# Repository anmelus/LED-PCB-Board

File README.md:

## LED Board project

This project demonstrates the design and development of a custom LED board, starting from PCB creation using KiCAD to writing the software that powers it. Below, you'll find details on how the project is structured and how to get started.

### Overview

This project involves the complete design and implementation of a custom LED board. It includes:

1. The PCB Design created using KiCAD.
2. The software to control the LED board, providing functionality such as LED patterns, brightness control, and more.

This repository serves as a resource for hobbyists and developers who want to understand the process of creating hardware and writing corresponding software.

### Features

Features

* Custom PCB Design: Created using KiCAD for a fully custom LED board.
* Software Integration: Firmware/software to control LEDs with custom patterns and behavior.
* Modular Design: Easy to modify and expand upon.

Images of the schematics and final result are available in /electrical/LEDboard/Images

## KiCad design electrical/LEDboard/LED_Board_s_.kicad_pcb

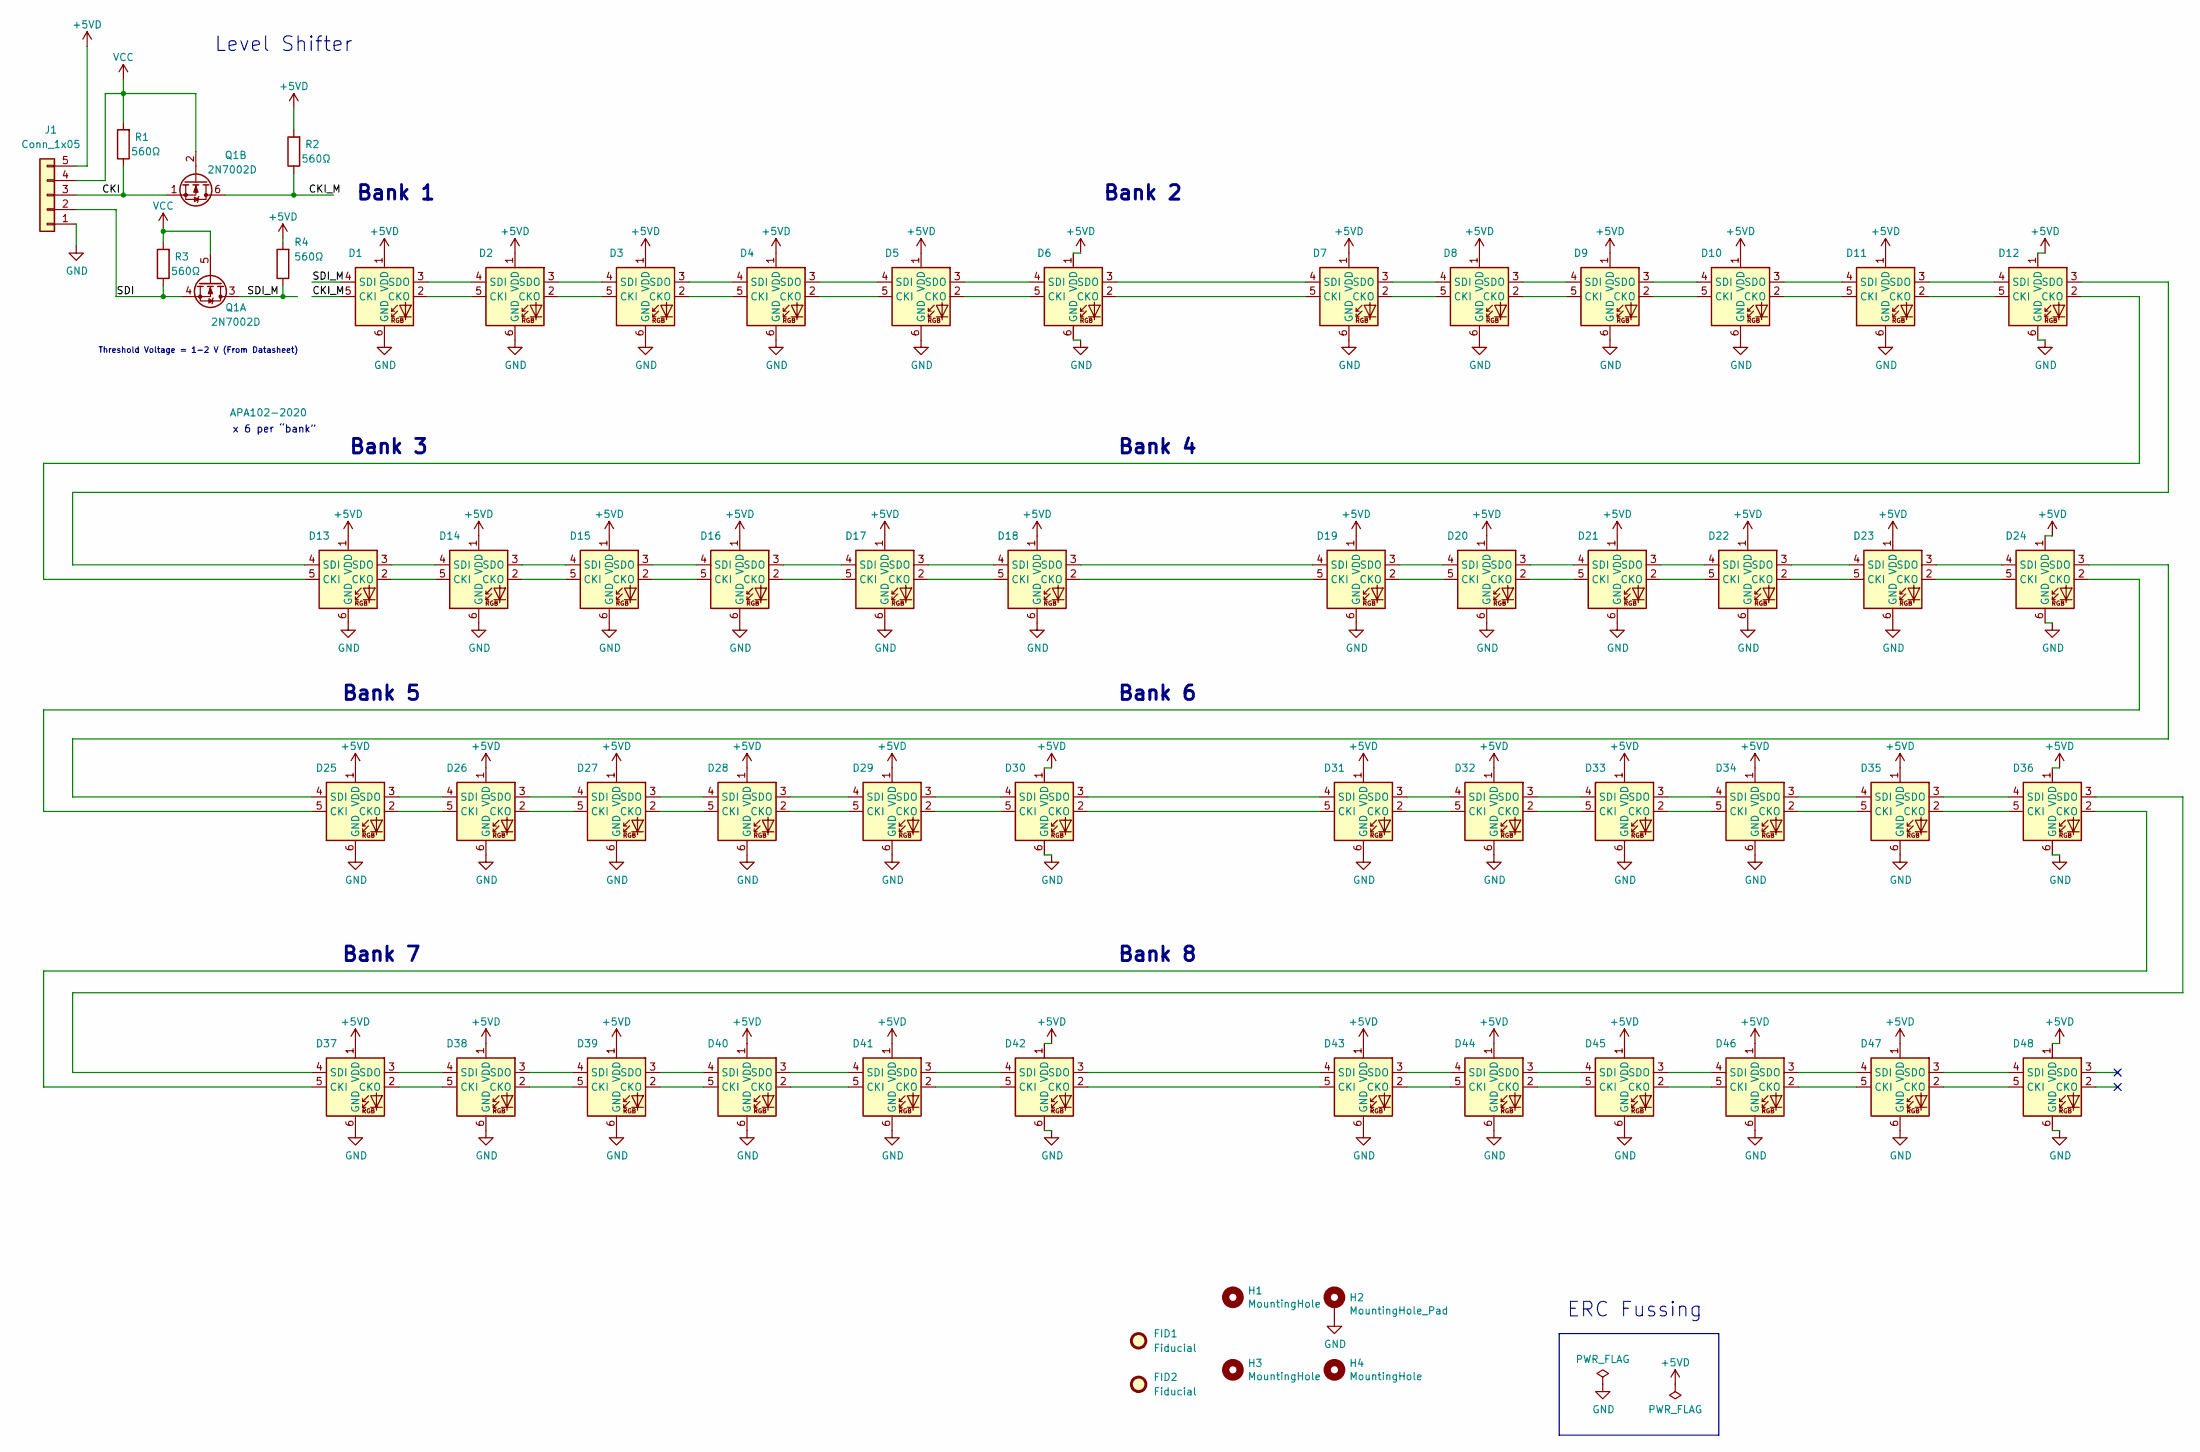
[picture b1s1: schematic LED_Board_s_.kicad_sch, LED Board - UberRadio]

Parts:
D1, D2, D3, D4, D5, D6, D7, D8, D9, D10, D11, D12, D13, D14, D15, D16, D17, D18, D19, D20, D21, D22, D23, D24, D25, D26, D27, D28, D29, D30, D31, D32, D33, D34, D35, D36, D37, D38, D39, D40, D41, D42, D43, D44, D45, D46, D47, D48: APA102-2020; LED-APA102-2020
FID1, FID2: Fiducial; Fiducial_0.5mm_Mask1mm
H1, H3, H4: MountingHole; MountingHole_3.5mm_Pad
H2: MountingHole_Pad; MountingHole_3.5mm_Pad_Via
J1: Conn_1x05; PinHeader_1x05_P2.54mm_Vertical
Q1: 2N7002D; SOT-23-6
R1, R2, R3, R4: 560Ω; R_1206_3216Metric_Pad1.30x1.75mm_HandSolder

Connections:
+5VD: D1.1 (VDD), D2.1 (VDD), D3.1 (VDD), D4.1 (VDD), D5.1 (VDD), D6.1 (VDD), D7.1 (VDD), D8.1 (VDD), D9.1 (VDD), D10.1 (VDD), D11.1 (VDD), D12.1 (VDD), D13.1 (VDD), D14.1 (VDD), D15.1 (VDD), D16.1 (VDD), D17.1 (VDD), D18.1 (VDD), D19.1 (VDD), D20.1 (VDD), D21.1 (VDD), D22.1 (VDD), D23.1 (VDD), D24.1 (VDD), D25.1 (VDD), D26.1 (VDD), D27.1 (VDD), D28.1 (VDD), D29.1 (VDD), D30.1 (VDD), D31.1 (VDD), D32.1 (VDD), D33.1 (VDD), D34.1 (VDD), D35.1 (VDD), D36.1 (VDD), D37.1 (VDD), D38.1 (VDD), D39.1 (VDD), D40.1 (VDD), D41.1 (VDD), D42.1 (VDD), D43.1 (VDD), D44.1 (VDD), D45.1 (VDD), D46.1 (VDD), D47.1 (VDD), D48.1 (VDD), J1.5, R2.2, R4.2
/CKI: J1.3, Q1.1 (S), R1.1
/CKI_M: D1.5 (CKI), Q1.6 (D), R2.1
/SDI: J1.2, Q1.4 (S), R3.1
/SDI_M: D1.4 (SDI), Q1.3 (D), R4.1
GND: D1.6 (GND), D2.6 (GND), D3.6 (GND), D4.6 (GND), D5.6 (GND), D6.6 (GND), D7.6 (GND), D8.6 (GND), D9.6 (GND), D10.6 (GND), D11.6 (GND), D12.6 (GND), D13.6 (GND), D14.6 (GND), D15.6 (GND), D16.6 (GND), D17.6 (GND), D18.6 (GND), D19.6 (GND), D20.6 (GND), D21.6 (GND), D22.6 (GND), D23.6 (GND), D24.6 (GND), D25.6 (GND), D26.6 (GND), D27.6 (GND), D28.6 (GND), D29.6 (GND), D30.6 (GND), D31.6 (GND), D32.6 (GND), D33.6 (GND), D34.6 (GND), D35.6 (GND), D36.6 (GND), D37.6 (GND), D38.6 (GND), D39.6 (GND), D40.6 (GND), D41.6 (GND), D42.6 (GND), D43.6 (GND), D44.6 (GND), D45.6 (GND), D46.6 (GND), D47.6 (GND), D48.6 (GND), H2.1, J1.1
unnamed: D1.2 (CKO), D2.5 (CKI)
unnamed: D1.3 (SDO), D2.4 (SDI)
unnamed: D2.2 (CKO), D3.5 (CKI)
unnamed: D2.3 (SDO), D3.4 (SDI)
unnamed: D3.2 (CKO), D4.5 (CKI)
unnamed: D3.3 (SDO), D4.4 (SDI)
unnamed: D4.2 (CKO), D5.5 (CKI)
unnamed: D4.3 (SDO), D5.4 (SDI)
unnamed: D5.2 (CKO), D6.5 (CKI)
unnamed: D5.3 (SDO), D6.4 (SDI)
unnamed: D6.2 (CKO), D7.5 (CKI)
unnamed: D6.3 (SDO), D7.4 (SDI)
unnamed: D7.2 (CKO), D8.5 (CKI)
unnamed: D7.3 (SDO), D8.4 (SDI)
unnamed: D8.2 (CKO), D9.5 (CKI)
unnamed: D8.3 (SDO), D9.4 (SDI)
unnamed: D10.2 (CKO), D11.5 (CKI)
unnamed: D10.3 (SDO), D11.4 (SDI)
unnamed: D9.3 (SDO), D10.4 (SDI)
unnamed: D9.2 (CKO), D10.5 (CKI)
unnamed: D11.2 (CKO), D12.5 (CKI)
unnamed: D11.3 (SDO), D12.4 (SDI)
unnamed: D12.2 (CKO), D13.5 (CKI)
unnamed: D12.3 (SDO), D13.4 (SDI)
unnamed: D13.2 (CKO), D14.5 (CKI)
unnamed: D13.3 (SDO), D14.4 (SDI)
unnamed: D14.2 (CKO), D15.5 (CKI)
unnamed: D14.3 (SDO), D15.4 (SDI)
unnamed: D15.2 (CKO), D16.5 (CKI)
unnamed: D15.3 (SDO), D16.4 (SDI)
unnamed: D16.2 (CKO), D17.5 (CKI)
unnamed: D16.3 (SDO), D17.4 (SDI)
unnamed: D17.2 (CKO), D18.5 (CKI)
unnamed: D17.3 (SDO), D18.4 (SDI)
unnamed: D18.2 (CKO), D19.5 (CKI)
unnamed: D18.3 (SDO), D19.4 (SDI)
unnamed: D19.2 (CKO), D20.5 (CKI)
unnamed: D19.3 (SDO), D20.4 (SDI)
unnamed: D20.2 (CKO), D21.5 (CKI)
unnamed: D20.3 (SDO), D21.4 (SDI)
unnamed: D21.2 (CKO), D22.5 (CKI)
unnamed: D21.3 (SDO), D22.4 (SDI)
unnamed: D22.2 (CKO), D23.5 (CKI)
unnamed: D22.3 (SDO), D23.4 (SDI)
unnamed: D23.2 (CKO), D24.5 (CKI)
unnamed: D23.3 (SDO), D24.4 (SDI)
unnamed: D24.2 (CKO), D25.5 (CKI)
unnamed: D24.3 (SDO), D25.4 (SDI)
unnamed: D25.2 (CKO), D26.5 (CKI)
unnamed: D25.3 (SDO), D26.4 (SDI)
unnamed: D26.2 (CKO), D27.5 (CKI)
unnamed: D26.3 (SDO), D27.4 (SDI)
unnamed: D27.2 (CKO), D28.5 (CKI)
unnamed: D27.3 (SDO), D28.4 (SDI)
unnamed: D28.2 (CKO), D29.5 (CKI)
unnamed: D28.3 (SDO), D29.4 (SDI)
unnamed: D29.2 (CKO), D30.5 (CKI)
unnamed: D29.3 (SDO), D30.4 (SDI)
unnamed: D30.2 (CKO), D31.5 (CKI)
unnamed: D30.3 (SDO), D31.4 (SDI)
unnamed: D31.2 (CKO), D32.5 (CKI)
unnamed: D31.3 (SDO), D32.4 (SDI)
unnamed: D32.2 (CKO), D33.5 (CKI)
unnamed: D32.3 (SDO), D33.4 (SDI)
unnamed: D33.2 (CKO), D34.5 (CKI)
unnamed: D33.3 (SDO), D34.4 (SDI)
unnamed: D34.2 (CKO), D35.5 (CKI)
unnamed: D34.3 (SDO), D35.4 (SDI)
unnamed: D35.2 (CKO), D36.5 (CKI)
unnamed: D35.3 (SDO), D36.4 (SDI)
unnamed: D36.2 (CKO), D37.5 (CKI)
unnamed: D36.3 (SDO), D37.4 (SDI)
unnamed: D37.2 (CKO), D38.5 (CKI)
unnamed: D37.3 (SDO), D38.4 (SDI)
unnamed: D38.2 (CKO), D39.5 (CKI)
unnamed: D38.3 (SDO), D39.4 (SDI)
unnamed: D39.2 (CKO), D40.5 (CKI)
unnamed: D39.3 (SDO), D40.4 (SDI)
unnamed: D40.2 (CKO), D41.5 (CKI)
unnamed: D40.3 (SDO), D41.4 (SDI)
unnamed: D41.2 (CKO), D42.5 (CKI)
unnamed: D41.3 (SDO), D42.4 (SDI)
unnamed: D42.2 (CKO), D43.5 (CKI)
unnamed: D42.3 (SDO), D43.4 (SDI)
unnamed: D43.2 (CKO), D44.5 (CKI)
unnamed: D43.3 (SDO), D44.4 (SDI)
unnamed: D44.2 (CKO), D45.5 (CKI)
unnamed: D44.3 (SDO), D45.4 (SDI)
unnamed: D45.2 (CKO), D46.5 (CKI)
unnamed: D45.3 (SDO), D46.4 (SDI)
unnamed: D46.2 (CKO), D47.5 (CKI)
unnamed: D46.3 (SDO), D47.4 (SDI)
unnamed: D47.2 (CKO), D48.5 (CKI)
unnamed: D47.3 (SDO), D48.4 (SDI)
VCC: J1.4, Q1.2 (G), Q1.5 (G), R1.2, R3.2

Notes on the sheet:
Bank 5
Bank 3
x 6 per “bank”
Bank 4
Bank 6
Bank 2
ERC Fussing
Threshold Voltage = 1-2 V (From Datasheet)
Level Shifter
Bank 8
Bank 1
Bank 7

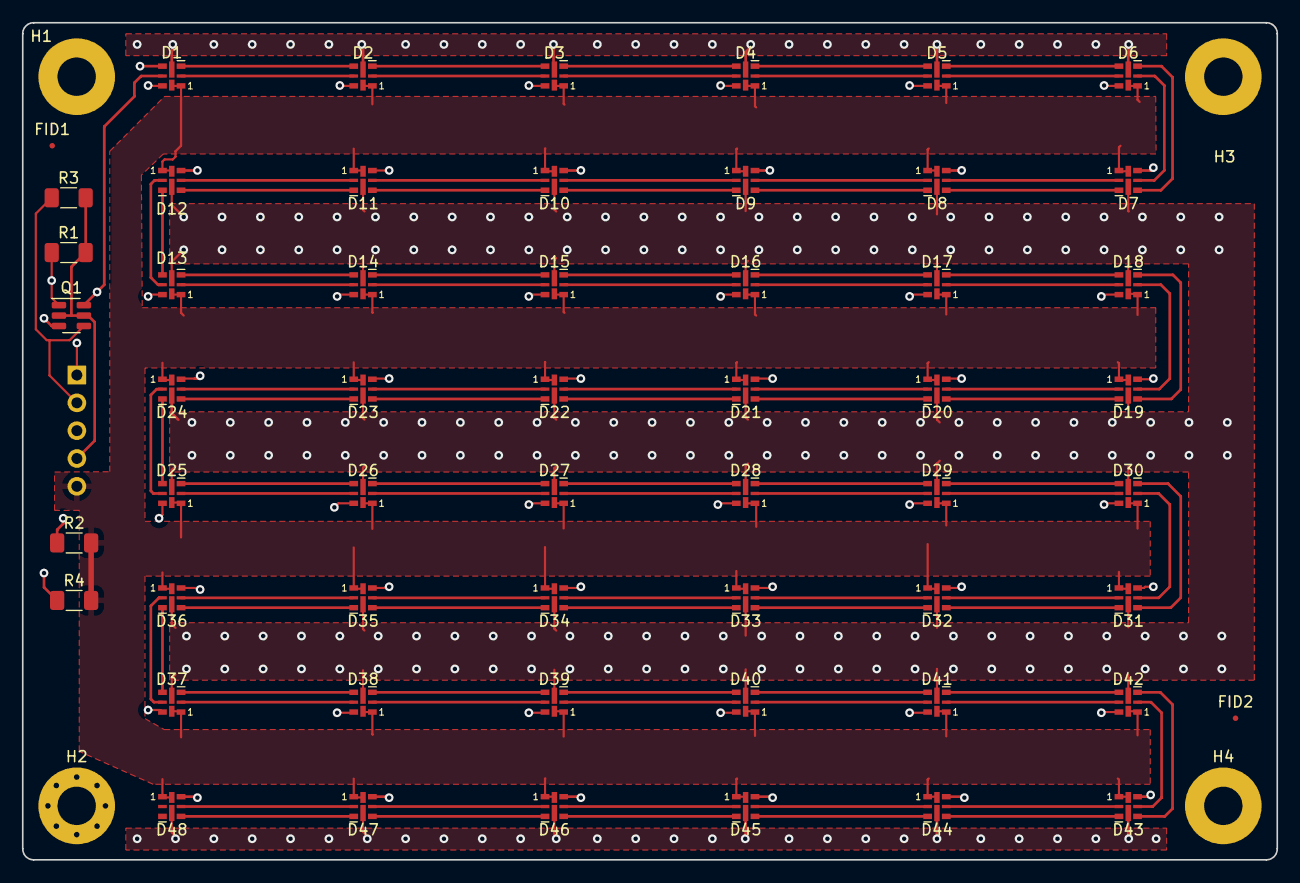
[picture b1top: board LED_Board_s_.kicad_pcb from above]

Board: 4 copper layers, 114.5 x 76.4 mm, 60 parts (1 on the bottom side), 101 nets.

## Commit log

2025-01-07 Added files
